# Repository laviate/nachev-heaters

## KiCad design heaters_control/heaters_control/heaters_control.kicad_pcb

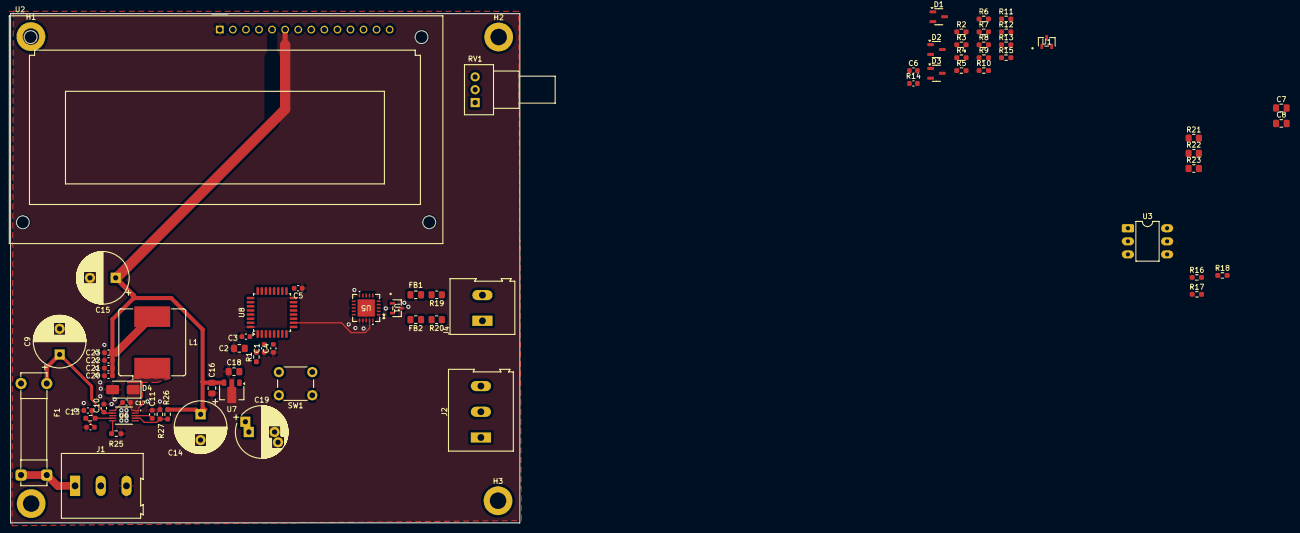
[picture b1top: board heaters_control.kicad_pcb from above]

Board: 2 copper layers, 99.0 x 99.0 mm, 75 parts (0 on the bottom side), 46 nets.

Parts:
C1, C3, C4, C5, C6, C17: 100n; C_0603_1608Metric
C2, C16, C18: 10u; C_0805_2012Metric_Pad1.18x1.45mm_HandSolder
C7: 0805 1u; C_0805_2012Metric_Pad1.18x1.45mm_HandSolder
C8: 0805 100n; C_0805_2012Metric_Pad1.18x1.45mm_HandSolder
C9, C14, C15: 330u; CP_Radial_D10.0mm_P5.00mm
C10: 4.7u; C_0603_1608Metric
C11: 6.8p; C_0603_1608Metric
C12: 2.7n; C_0603_1608Metric
C13: 6.8n; C_0603_1608Metric
C19: 330u; CP_Radial_D10.0mm_P5.00mm_P7.50mm
C20, C21, C22, C23: 22u; C_0603_1608Metric
D1, D2, D3: PESD5V2S2UT; SOT-23-3
D4: SS24; D_SMA
F1: Fuse; Fuseholder_Clip-5x20mm_Bel_FC-203-22_Lateral_P17.80x5.00mm_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
FB1, FB2: FerriteBead; C_0805_2012Metric_Pad1.18x1.45mm_HandSolder
H1, H2, H3, H4: MountingHole; MountingHole_3.2mm_M3_DIN965_Pad
J1, J2: Screw_Terminal_01x03; TerminalBlock_Altech_AK300-3_P5.00mm
J4: Screw_Terminal_01x02; TerminalBlock_Altech_AK300-2_P5.00mm
L1: 47u; L_Bourns_SRR1208_12.7x12.7mm
R1, R2, R27: 10k; R_0603_1608Metric_Pad0.98x0.95mm_HandSolder
R3, R4, R7, R8, R9, R10, R11, R12, R13, R15: 5.1k; R_0603_1608Metric_Pad0.98x0.95mm_HandSolder
R5, R6: 20k; R_0603_1608Metric_Pad0.98x0.95mm_HandSolder
R14: 5.1k; C_0603_1608Metric
R16, R17: 180R; R_0603_1608Metric_Pad0.98x0.95mm_HandSolder
R18: 390R; R_0603_1608Metric_Pad0.98x0.95mm_HandSolder
R19, R20: 100R 1%; R_0805_2012Metric_Pad1.20x1.40mm_HandSolder
R21: 2M 1%; R_0805_2012Metric_Pad1.20x1.40mm_HandSolder
R22: 2.49M 1%; R_0805_2012Metric_Pad1.20x1.40mm_HandSolder
R23: 487k 1%; R_0805_2012Metric_Pad1.20x1.40mm_HandSolder
R24: 105k; R_0603_1608Metric_Pad0.98x0.95mm_HandSolder
R25: 255k; R_0603_1608Metric_Pad0.98x0.95mm_HandSolder
R26: 52.3k; R_0603_1608Metric_Pad0.98x0.95mm_HandSolder
RV1: R_Potentiometer; Potentiometer_Alps_RK09Y11_Single_Horizontal
SW1: SW_Push; SW_PUSH_6mm
U1, U1#2: PESD3V3S2UT; SOT23_NEX-L
U2: WH1602B-TMI-CT; LM16255
U3: MOC3063M; DIP-6_W7.62mm_LongPads
U5: MCP96L01-E/MX; MQFN20_NU_MCH
U6: TPS54140ADGQ; DGQ10_1P88X1P57_TEX
U7: AX1007E33A; SOT-89-3
U8: STM32L010K4Tx; LQFP-32_7x7mm_P0.8mm

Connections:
24_DC: F1.1, J1.1
24_FUSED: C9.1, C10.1, F1.2, R16.1, U6.2 (VIN), U6.3 (EN)
+3.3V: C2.2, C3.2, C4.2, C5.2, C7.1, C18.1, C19.1, R1.1, R5.1, R6.1, R21.1, U5.8 (VDD), U7.1 (OUT), U8.1 (VDD), U8.5 (VDDA), U8.17 (VDD)
+5V: C6.1, C14.1, C15.1, C16.1, C20.1, C21.1, C22.1, C23.1, L1.2, R3.1, R4.1, R7.1, R8.1, R9.1, R10.1, R11.1, R12.1, R13.1, R14.1, R26.1, U2.2 (VDD), U2.6 (E), U7.3 (IN)
GND: C1.1, C2.1, C3.1, C4.1, C5.1, C6.2, C7.2, C9.2, C10.2, C11.2, C12.2, C13.2, C14.2, C15.2, C16.2, C18.2, C19.2, C20.2, C21.2, C22.2, C23.2, D1.3 (A), D2.3 (A), D3.3 (A), D4.2 (A), J1.3, R2.2, R15.2, R22.2, R23.1, R25.2, R27.2, SW1.1, U1.3, U1#2.3, U2.1 (VSS), U3.2, U5.1 (GND), U5.3 (GND), U5.5 (GND), U5.10 (GND), U5.13 (GND), U5.16 (ADDR), U5.17 (GND), U5.18 (GND), U5.21 (GND), U6.9 (GND), U7.2 (GND), U8.16 (VSS), U8.32 (VSS)
I2C_SCL: R5.2, U5.19 (SCL), U8.10 (PA4)
I2C_SDA: R6.2, U5.20 (SDA), U8.20 (PA10)
MD0_TEMP_CONTROL: R18.1, U8.25 (PA15)
MDI_ALERT1: U5.11 (ALERT1), U8.14 (PB0)
MDI_ALERT2: U5.12 (ALERT2), U8.15 (PB1)
MDI_ALERT3: U5.14 (ALERT3), U8.26 (PB3)
MDI_ALERT4: U5.15 (ALERT4), U8.27 (PB4)
MDI_OCALERT: U5.9 (OC_ALERT), U8.28 (PB5)
MDI_SCALERT: U5.7 (SC_ALERT), U8.29 (PB6)
unnamed: C12.1, R24.2
unnamed: C17.2, D4.1 (K), L1.1, U6.10 (PH)
unnamed: FB1.1, R19.2
unnamed: FB2.1, R20.2
unnamed: J4.1, R20.1
unnamed: J4.2, R19.1
unnamed: R14.2, RV1.1
unnamed: R15.1, RV1.3
unnamed: R16.2, R17.1
unnamed: R17.2, U3.6
unnamed: R18.2, U3.1
unnamed: R7.2, U2.7 (DB0), U8.12 (PA6)
unnamed: R8.2, U2.8 (DB1), U8.13 (PA7)
unnamed: R9.2, U2.9 (DB2), U8.18 (PA8)
unnamed: D2.1 (K), R10.2, U2.10 (DB3), U8.19 (PA9)
unnamed: D2.2 (K), R11.2, U2.11 (DB4), U8.21 (PA11)
unnamed: D3.1 (K), R12.2, U2.12 (DB5), U8.22 (PA12)
unnamed: D3.2 (K), R13.2, U2.13 (DB6), U8.23 (PA13)
unnamed: U2.14 (DB7), U8.24 (PA14)
unnamed: D1.1 (K), R3.2, U2.4 (RS), U8.7 (PA1)
unnamed: D1.2 (K), R4.2, U2.5 (R/W), U8.9 (PA3)
unnamed: RV1.2, U2.3 (VO)
unnamed: C8.2, FB2.2, R21.2, R22.1, U1.2, U1#2.2, U5.2 (VIN+), U5.6 (VSENSE)
unnamed: C8.1, FB1.2, R23.2, U1.1, U1#2.1, U5.4 (VIN-)
unnamed: C17.1, U6.1 (BOOT)
unnamed: C11.1, U6.8 (COMP)
unnamed: R25.1, U6.5 (RT/CLK)
unnamed: C13.1, R24.1, U6.4 (SS/TR)
unnamed: R26.2, R27.1, U6.7 (VSENSE)
unnamed: C1.2, R1.2, SW1.2, U8.4 (NRST)
unnamed: R2.1, U8.31 (PB9)
PO_GATE_THYR: J2.3, U3.4

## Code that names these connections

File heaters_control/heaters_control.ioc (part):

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Mcu.Name=STM32L010K4Tx
Mcu.Package=LQFP32
Mcu.UserName=STM32L010K4Tx
PA0-CK_IN.Signal=GPIO_Output
PA1.Signal=GPIO_Output
PA10.Mode=I2C
PA10.Signal=I2C1_SDA
PA11.Signal=GPIO_Output
PA2.Signal=GPIO_Output
PA3.Signal=GPIO_Output
PA4.Mode=I2C
PA4.Signal=I2C1_SCL
PA5.Signal=GPIO_Output
PA6.Signal=GPIO_Output
PA7.Signal=GPIO_Output
PA8.Signal=GPIO_Output
PA9.Signal=GPIO_Output
PB3.Signal=GPIO_Input
PB4.Signal=GPIO_Input
PB5.Signal=GPIO_Input
PB6.Signal=GPIO_Input
PB7.Signal=GPIO_Input
PB9-BOOT0.Signal=GPIO_Input
RCC.HSE_VALUE=8000000
RCC.SYSCLKFreq_VALUE=16000000
RCC.SYSCLKSource=RCC_SYSCLKSOURCE_HSI
board=custom

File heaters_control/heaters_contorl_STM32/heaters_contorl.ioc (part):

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Mcu.Name=STM32L010K4Tx
Mcu.Package=LQFP32
Mcu.UserName=STM32L010K4Tx
PA1.GPIOParameters=GPIO_PuPd,GPIO_ModeDefaultOutputPP
PA1.GPIO_ModeDefaultOutputPP=GPIO_MODE_OUTPUT_OD
PA1.GPIO_PuPd=GPIO_NOPULL
PA1.Signal=GPIO_Output
PA10.Mode=I2C
PA10.Signal=I2C1_SDA
PA11.GPIOParameters=GPIO_PuPd,GPIO_ModeDefaultOutputPP
PA11.GPIO_ModeDefaultOutputPP=GPIO_MODE_OUTPUT_OD
PA11.GPIO_PuPd=GPIO_NOPULL
PA11.Signal=GPIO_Output
PA12.GPIOParameters=GPIO_PuPd,GPIO_ModeDefaultOutputPP
PA12.GPIO_ModeDefaultOutputPP=GPIO_MODE_OUTPUT_OD
PA12.GPIO_PuPd=GPIO_NOPULL
PA12.Signal=GPIO_Output
PA13.GPIOParameters=GPIO_PuPd,GPIO_ModeDefaultOutputPP
PA13.GPIO_ModeDefaultOutputPP=GPIO_MODE_OUTPUT_OD
PA13.GPIO_PuPd=GPIO_NOPULL
PA13.Signal=GPIO_Output
PA14.GPIOParameters=GPIO_PuPd,GPIO_ModeDefaultOutputPP
PA14.GPIO_ModeDefaultOutputPP=GPIO_MODE_OUTPUT_OD
PA14.GPIO_PuPd=GPIO_NOPULL
PA14.Signal=GPIO_Output
PA3.GPIOParameters=GPIO_PuPd,GPIO_ModeDefaultOutputPP
PA3.GPIO_ModeDefaultOutputPP=GPIO_MODE_OUTPUT_OD
PA3.GPIO_PuPd=GPIO_NOPULL
PA3.Signal=GPIO_Output
PA4.Mode=I2C
PA4.Signal=I2C1_SCL
PA6.GPIOParameters=GPIO_PuPd,GPIO_ModeDefaultOutputPP
PA6.GPIO_ModeDefaultOutputPP=GPIO_MODE_OUTPUT_OD
PA6.GPIO_PuPd=GPIO_NOPULL
PA6.Signal=GPIO_Output
PA7.GPIOParameters=GPIO_PuPd,GPIO_ModeDefaultOutputPP
PA7.GPIO_ModeDefaultOutputPP=GPIO_MODE_OUTPUT_OD
PA7.GPIO_PuPd=GPIO_NOPULL
PA7.Signal=GPIO_Output
PA8.GPIOParameters=GPIO_PuPd,GPIO_ModeDefaultOutputPP
PA8.GPIO_ModeDefaultOutputPP=GPIO_MODE_OUTPUT_OD
PA8.GPIO_PuPd=GPIO_NOPULL
PA8.Signal=GPIO_Output
PA9.GPIOParameters=GPIO_PuPd,GPIO_ModeDefaultOutputPP
PA9.GPIO_ModeDefaultOutputPP=GPIO_MODE_OUTPUT_OD
PA9.GPIO_PuPd=GPIO_NOPULL
PA9.Signal=GPIO_Output
RCC.HSE_VALUE=8000000
RCC.SYSCLKFreq_VALUE=16000000
RCC.SYSCLKSource=RCC_SYSCLKSOURCE_HSI
board=custom

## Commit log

2025-09-02 Add gitignore
